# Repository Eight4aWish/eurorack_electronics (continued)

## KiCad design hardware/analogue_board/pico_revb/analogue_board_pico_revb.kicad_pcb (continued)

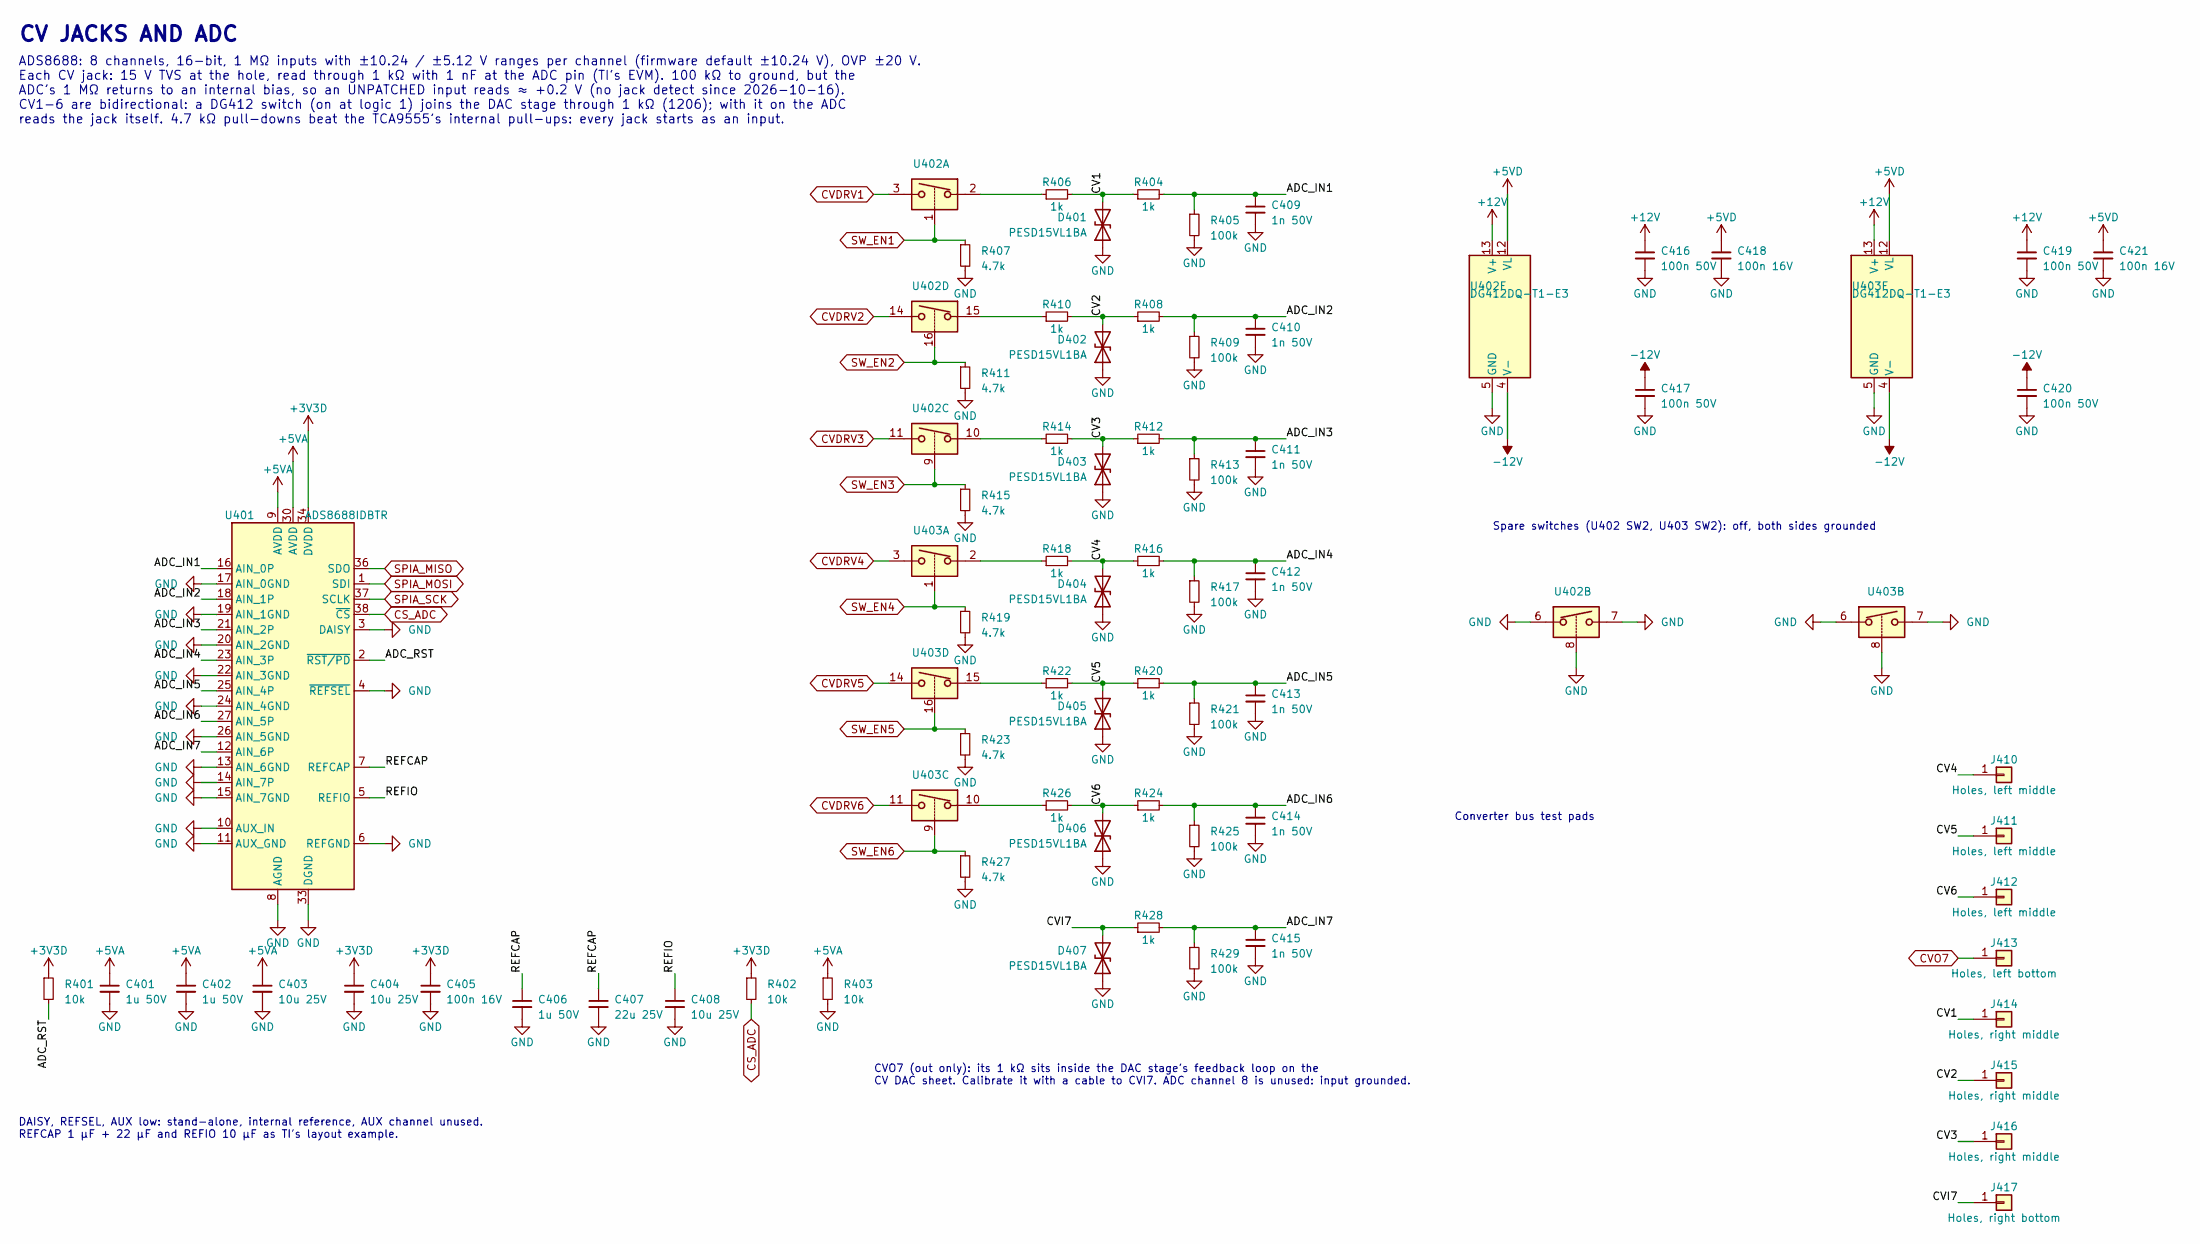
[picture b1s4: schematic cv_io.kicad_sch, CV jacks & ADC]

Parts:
C401, C402, C406: 1u 50V; C_0603_1608Metric; Voltage 50V; LCSC C15849
C403, C404, C408: 10u 25V; C_0805_2012Metric; Voltage 25V; LCSC C15850
C405, C418, C421: 100n 16V; C_0402_1005Metric; Voltage 16V; LCSC C1525
C407: 22u 25V; C_1206_3216Metric; Voltage 25V; LCSC C12891
C409, C410, C411, C412, C413, C414, C415: 1n 50V; C_0402_1005Metric; Voltage 50V; LCSC C1523
C416, C417, C419, C420: 100n 50V; C_0603_1608Metric; Voltage 50V; LCSC C14663
D401, D402, D403, D404, D405, D406, D407: PESD15VL1BA; D_SOD-323; MPN PESD15VL1BA,115; LCSC C85378
J410, J411, J412: Holes, left middle; WiringHoles_1x01; JLC bare holes
J413: Holes, left bottom; WiringHoles_1x01; JLC bare holes
J414, J415, J416: Holes, right middle; WiringHoles_1x01; JLC bare holes
J417: Holes, right bottom; WiringHoles_1x01; JLC bare holes
R401, R402, R403: 10k; R_0402_1005Metric; Tolerance 1%; LCSC C25744
R404, R408, R412, R416, R420, R424, R428: 1k; R_0402_1005Metric; Tolerance 1%; LCSC C11702
R405, R409, R413, R417, R421, R425, R429: 100k; R_0402_1005Metric; Tolerance 1%; LCSC C25741
R406, R410, R414, R418, R422, R426: 1k; R_1206_3216Metric; Tolerance 1%; LCSC C4410
R407, R411, R415, R419, R423, R427: 4.7k; R_0402_1005Metric; Tolerance 1%; LCSC C25900
U401: ADS8688IDBTR; TSSOP-38_4.4x9.7mm_P0.5mm; MPN ADS8688IDBTR; LCSC C527390
U402, U403: DG412DQ-T1-E3; TSSOP-16_4.4x5mm_P0.65mm; MPN DG412DQ-T1-E3; LCSC C2651920

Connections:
+3V3D: C404.1, C405.1, R401.1, R402.1, U401.34 (DVDD); also elsewhere on the board
+5VA: C401.1, C402.1, C403.1, R403.1, U401.9 (AVDD), U401.30 (AVDD); also elsewhere on the board
+5VD: C418.1, C421.1, U402.12 (VL), U403.12 (VL); also elsewhere on the board
+12V: C416.1, C419.1, U402.13 (V+), U403.13 (V+); also elsewhere on the board
-12V: C417.1, C420.1, U402.4 (V-), U403.4 (V-); also elsewhere on the board
/CV jacks & ADC/ADC_IN1: C409.1, R404.2, R405.1, U401.16 (AIN_0P)
/CV jacks & ADC/ADC_IN2: C410.1, R408.2, R409.1, U401.18 (AIN_1P)
/CV jacks & ADC/ADC_IN3: C411.1, R412.2, R413.1, U401.21 (AIN_2P)
/CV jacks & ADC/ADC_IN4: C412.1, R416.2, R417.1, U401.23 (AIN_3P)
/CV jacks & ADC/ADC_IN5: C413.1, R420.2, R421.1, U401.25 (AIN_4P)
/CV jacks & ADC/ADC_IN6: C414.1, R424.2, R425.1, U401.27 (AIN_5P)
/CV jacks & ADC/ADC_IN7: C415.1, R428.2, R429.1, U401.12 (AIN_6P)
/CV jacks & ADC/ADC_RST: R401.2, U401.2 (~RST/PD)
/CV jacks & ADC/CV1: D401.2 (A2), J414.1, R404.1, R406.2
/CV jacks & ADC/CV2: D402.2 (A2), J415.1, R408.1, R410.2
/CV jacks & ADC/CV3: D403.2 (A2), J416.1, R412.1, R414.2
/CV jacks & ADC/CV4: D404.2 (A2), J410.1, R416.1, R418.2
/CV jacks & ADC/CV5: D405.2 (A2), J411.1, R420.1, R422.2
/CV jacks & ADC/CV6: D406.2 (A2), J412.1, R424.1, R426.2
/CV jacks & ADC/CVI7: D407.2 (A2), J417.1, R428.1
/CV jacks & ADC/REFCAP: C406.1, C407.1, U401.7 (REFCAP)
/CV jacks & ADC/REFIO: C408.1, U401.5 (REFIO)
CS_ADC: R402.2, U401.38 (~CS); also elsewhere on the board
CVDRV1: U402.3; also elsewhere on the board
CVDRV2: U402.14; also elsewhere on the board
CVDRV3: U402.11; also elsewhere on the board
CVDRV4: U403.3; also elsewhere on the board
CVDRV5: U403.14; also elsewhere on the board
CVDRV6: U403.11; also elsewhere on the board
CVO7: J413.1; also elsewhere on the board
GND: C401.2, C402.2, C403.2, C404.2, C405.2, C406.2, C407.2, C408.2, C409.2, C410.2, C411.2, C412.2, C413.2, C414.2, C415.2, C416.2, C417.2, C418.2, C419.2, C420.2, C421.2, D401.1 (A1), D402.1 (A1), D403.1 (A1), D404.1 (A1), D405.1 (A1), D406.1 (A1), D407.1 (A1), R403.2, R405.2, R407.2, R409.2, R411.2, R413.2, R415.2, R417.2, R419.2, R421.2, R423.2, R425.2, R427.2, R429.2, U401.3 (DAISY), U401.4 (~REFSEL), U401.6 (REFGND), U401.8 (AGND), U401.10 (AUX_IN), U401.11 (AUX_GND), U401.13 (AIN_6GND), U401.14 (AIN_7P), U401.15 (AIN_7GND), U401.17 (AIN_0GND), U401.19 (AIN_1GND), U401.20 (AIN_2GND), U401.22 (AIN_3GND), U401.24 (AIN_4GND), U401.26 (AIN_5GND), U401.28 (AGND), U401.29 (AGND), U401.31 (AGND), U401.32 (AGND), U401.33 (DGND), U402.5 (GND), U402.6, U402.7, U402.8, U403.5 (GND), U403.6, U403.7, U403.8; also elsewhere on the board
unnamed: R406.1, U402.2
unnamed: R410.1, U402.15
unnamed: R414.1, U402.10
unnamed: R418.1, U403.2
unnamed: R422.1, U403.15
unnamed: R426.1, U403.10
SPIA_MISO: U401.36 (SDO); also elsewhere on the board
SPIA_MOSI: U401.1 (SDI); also elsewhere on the board
SPIA_SCK: U401.37 (SCLK); also elsewhere on the board
SW_EN1: R407.1, U402.1; also elsewhere on the board
SW_EN2: R411.1, U402.16; also elsewhere on the board
SW_EN3: R415.1, U402.9; also elsewhere on the board
SW_EN4: R419.1, U403.1; also elsewhere on the board
SW_EN5: R423.1, U403.16; also elsewhere on the board
SW_EN6: R427.1, U403.9; also elsewhere on the board

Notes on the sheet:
CV JACKS AND ADC
ADS8688: 8 channels, 16-bit, 1 MΩ inputs with ±10.24 / ±5.12 V ranges per channel (firmware default ±10.24 V), OVP ±20 V. Each CV jack: 15 V TVS at the hole, read through 1 kΩ with 1 nF at the ADC pin (TI's EVM). 100 kΩ to ground, but the ADC's 1 MΩ returns to an internal bias, so an UNPATCHED inpu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
DAISY, REFSEL, AUX low: stand-alone, internal reference, AUX channel unused. REFCAP 1 µF + 22 µF and REFIO 10 µF as TI's layout example.
CVO7 (out only): its 1 kΩ sits inside the DAC stage's feedback loop on the CV DAC sheet. Calibrate it with a cable to CVI7. ADC channel 8 is unused: input grounded.
Spare switches (U402 SW2, U403 SW2): off, both sides grounded
Converter bus test pads

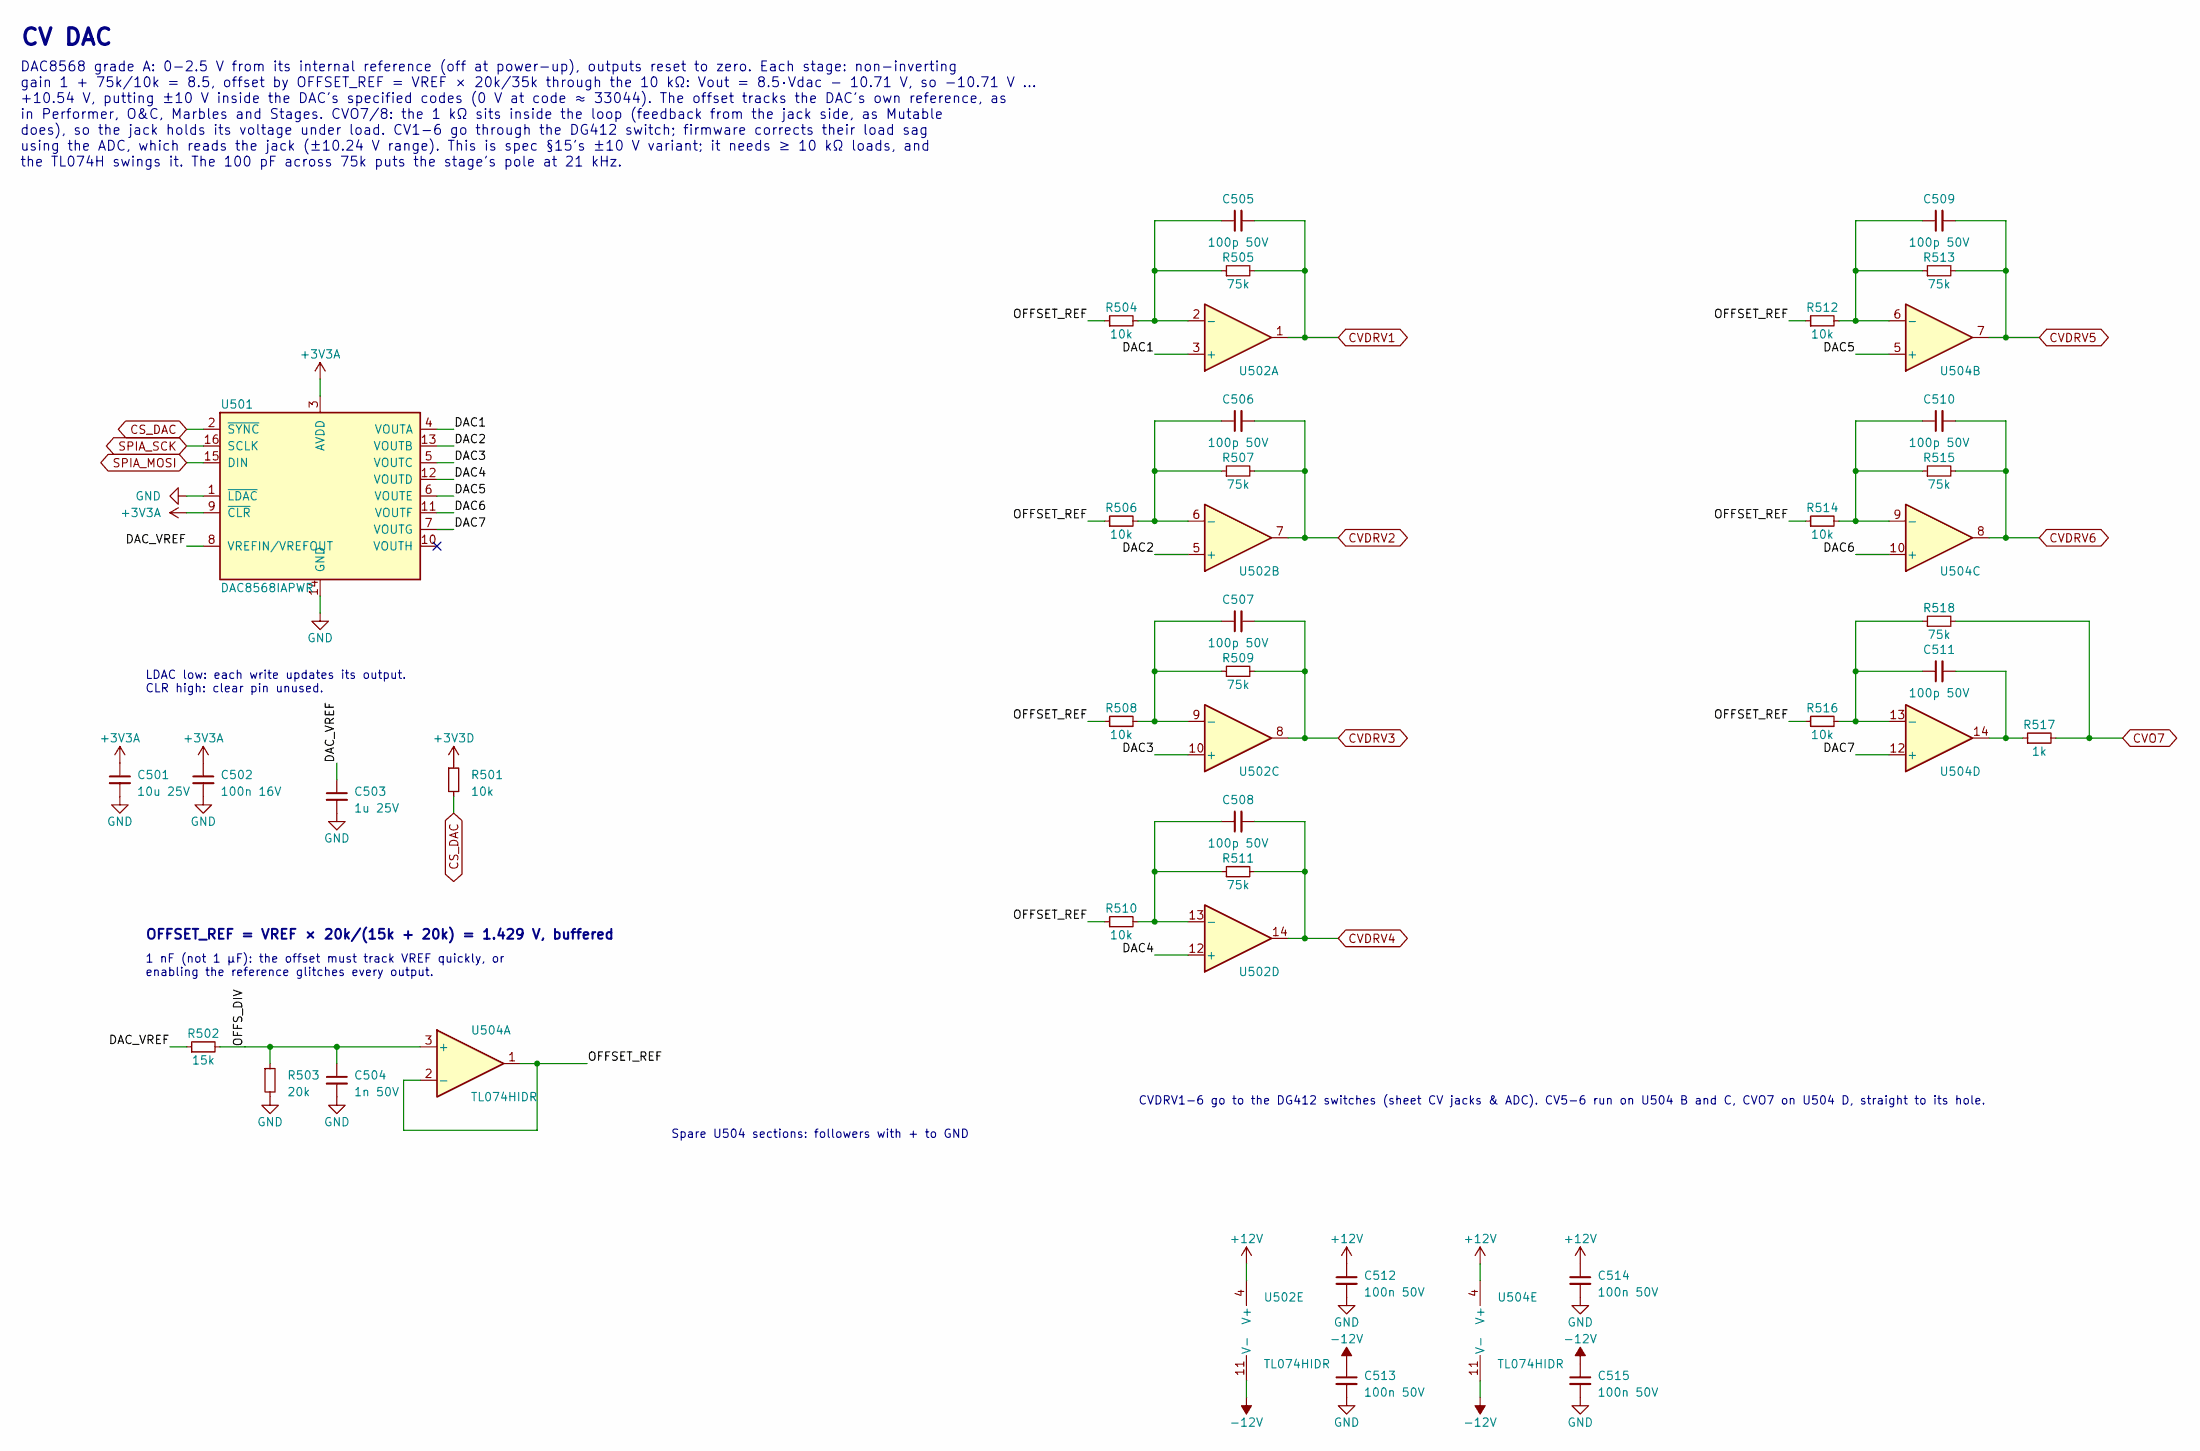
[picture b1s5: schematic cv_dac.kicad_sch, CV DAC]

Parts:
C501: 10u 25V; C_0805_2012Metric; Voltage 25V; LCSC C15850
C502: 100n 16V; C_0402_1005Metric; Voltage 16V; LCSC C1525
C503: 1u 25V; C_0402_1005Metric; Voltage 25V; LCSC C52923
C504: 1n 50V; C_0402_1005Metric; Voltage 50V; LCSC C1523
C505, C506, C507, C508, C509, C510, C511: 100p 50V; C_0402_1005Metric; Voltage 50V; LCSC C1546
C512, C513, C514, C515: 100n 50V; C_0603_1608Metric; Voltage 50V; LCSC C14663
R501, R504, R506, R508, R510, R512, R514, R516: 10k; R_0402_1005Metric; Tolerance 1%; LCSC C25744
R502: 15k; R_0402_1005Metric; Tolerance 1%; LCSC C25756
R503: 20k; R_0402_1005Metric; Tolerance 1%; LCSC C25765
R505, R507, R509, R511, R513, R515, R518: 75k; R_0603_1608Metric; Tolerance 1%; LCSC C23242
R517: 1k; R_1206_3216Metric; Tolerance 1%; LCSC C4410
U501: DAC8568IAPWR; TSSOP-16_4.4x5mm_P0.65mm; MPN DAC8568IAPWR; LCSC C486051
U502, U504: TL074HIDR; SOIC-14_3.9x8.7mm_P1.27mm; MPN TL074HIDR; LCSC C2878713

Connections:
+3V3A: C501.1, C502.1, U501.3 (AVDD), U501.9 (~CLR); also elsewhere on the board
+3V3D: R501.1; also elsewhere on the board
+12V: C512.1, C514.1, U502.4 (V+), U504.4 (V+); also elsewhere on the board
-12V: C513.1, C515.1, U502.11 (V-), U504.11 (V-); also elsewhere on the board
/CV DAC/DAC1: U501.4 (VOUTA), U502.3 (+)
/CV DAC/DAC2: U501.13 (VOUTB), U502.5 (+)
/CV DAC/DAC3: U501.5 (VOUTC), U502.10 (+)
/CV DAC/DAC4: U501.12 (VOUTD), U502.12 (+)
/CV DAC/DAC5: U501.6 (VOUTE), U504.5 (+)
/CV DAC/DAC6: U501.11 (VOUTF), U504.10 (+)
/CV DAC/DAC7: U501.7 (VOUTG), U504.12 (+)
/CV DAC/DAC_VREF: C503.1, R502.1, U501.8 (VREFIN/VREFOUT)
/CV DAC/OFFSET_REF: R504.1, R506.1, R508.1, R510.1, R512.1, R514.1, R516.1, U504.1, U504.2 (-)
/CV DAC/OFFS_DIV: C504.1, R502.2, R503.1, U504.3 (+)
CS_DAC: R501.2, U501.2 (~SYNC); also elsewhere on the board
CVDRV1: C505.2, R505.2, U502.1; also elsewhere on the board
CVDRV2: C506.2, R507.2, U502.7; also elsewhere on the board
CVDRV3: C507.2, R509.2, U502.8; also elsewhere on the board
CVDRV4: C508.2, R511.2, U502.14; also elsewhere on the board
CVDRV5: C509.2, R513.2, U504.7; also elsewhere on the board
CVDRV6: C510.2, R515.2, U504.8; also elsewhere on the board
CVO7: R517.2, R518.2; also elsewhere on the board
GND: C501.2, C502.2, C503.2, C504.2, C512.2, C513.2, C514.2, C515.2, R503.2, U501.1 (~LDAC), U501.14 (GND); also elsewhere on the board
unnamed: C511.2, R517.1, U504.14
unnamed: C505.1, R504.2, R505.1, U502.2 (-)
unnamed: C506.1, R506.2, R507.1, U502.6 (-)
unnamed: C507.1, R508.2, R509.1, U502.9 (-)
unnamed: C508.1, R510.2, R511.1, U502.13 (-)
unnamed: C509.1, R512.2, R513.1, U504.6 (-)
unnamed: C510.1, R514.2, R515.1, U504.9 (-)
unnamed: C511.1, R516.2, R518.1, U504.13 (-)
SPIA_MOSI: U501.15 (DIN); also elsewhere on the board
SPIA_SCK: U501.16 (SCLK); also elsewhere on the board

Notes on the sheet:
CV DAC
DAC8568 grade A: 0-2.5 V from its internal reference (off at power-up), outputs reset to zero. Each stage: non-inverting gain 1 + 75k/10k = 8.5, offset by OFFSET_REF = VREF × 20k/35k through the 10 kΩ: Vout = 8.5·Vdac − 10.71 V, so −10.71 V … +10.54 V, putting ±10 V inside the DAC's specified codes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
LDAC low: each write updates its output. CLR high: clear pin unused.
OFFSET_REF = VREF × 20k/(15k + 20k) = 1.429 V, buffered
1 nF (not 1 µF): the offset must track VREF quickly, or enabling the reference glitches every output.
CVDRV1-6 go to the DG412 switches (sheet CV jacks & ADC). CV5-6 run on U504 B and C, CVO7 on U504 D, straight to its hole.
Spare U504 sections: followers with + to GND

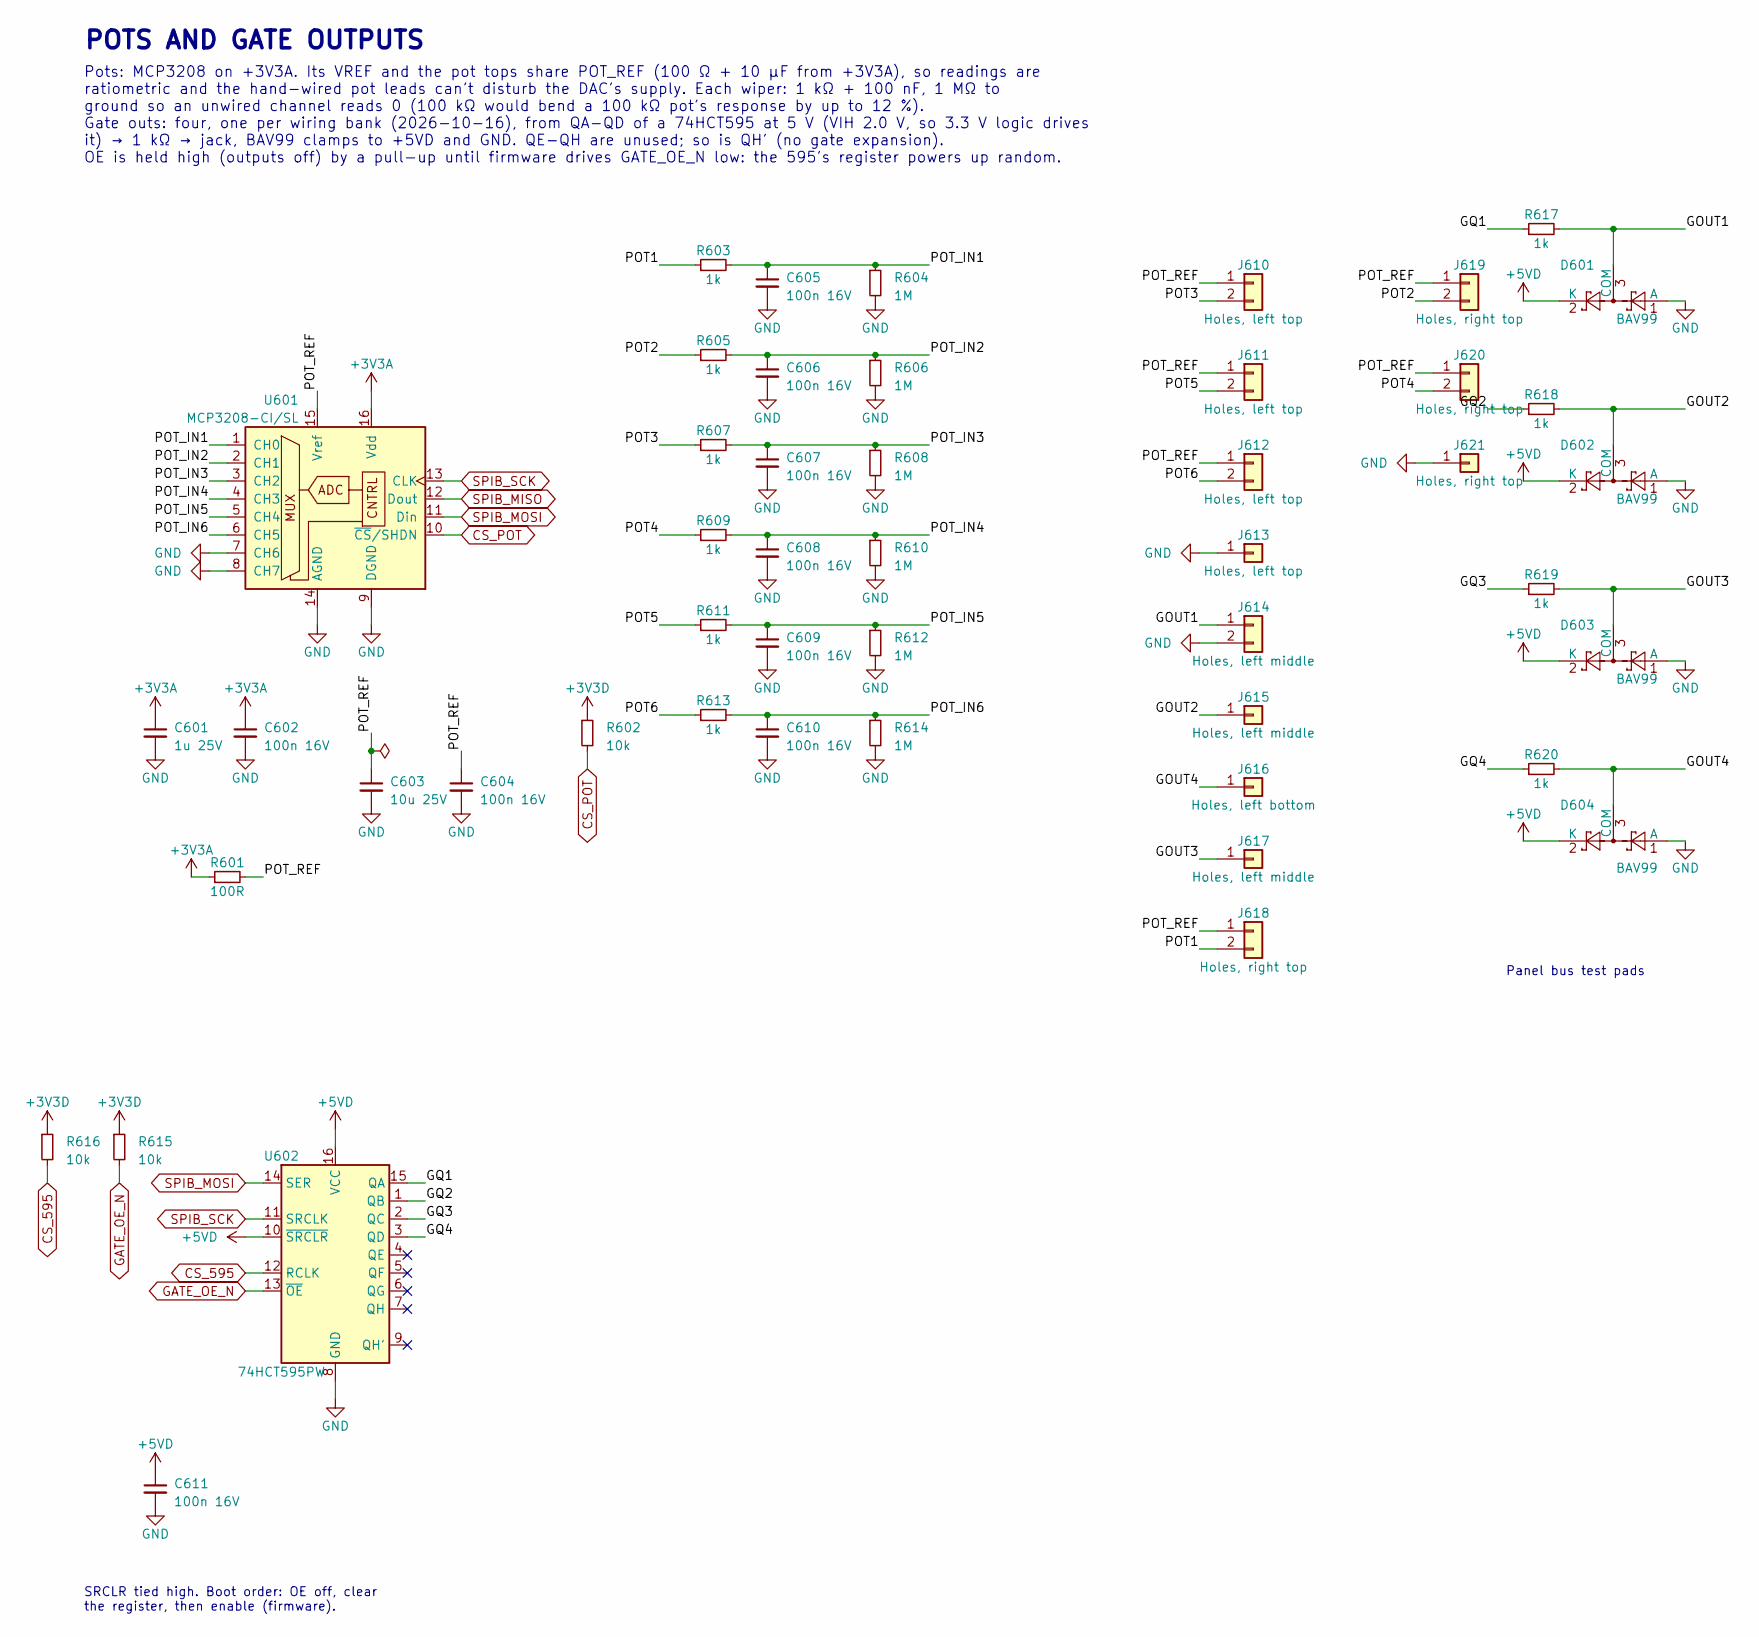
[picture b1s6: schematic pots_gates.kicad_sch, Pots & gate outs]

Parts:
C601: 1u 25V; C_0402_1005Metric; Voltage 25V; LCSC C52923
C602, C604, C605, C606, C607, C608, C609, C610, C611: 100n 16V; C_0402_1005Metric; Voltage 16V; LCSC C1525
C603: 10u 25V; C_0805_2012Metric; Voltage 25V; LCSC C15850
D601, D602, D603, D604: BAV99; SOT-23; MPN BAV99,215; LCSC C2500
J610, J611, J612: Holes, left top; WiringHoles_1x02; JLC bare holes
J613: Holes, left top; WiringHoles_1x01_G1; JLC bare holes
J614: Holes, left middle; WiringHoles_1x02_G2; JLC bare holes
J615, J617: Holes, left middle; WiringHoles_1x01; JLC bare holes
J616: Holes, left bottom; WiringHoles_1x01; JLC bare holes
J618, J619, J620: Holes, right top; WiringHoles_1x02; JLC bare holes
J621: Holes, right top; WiringHoles_1x01_G1; JLC bare holes
R601: 100R; R_0805_2012Metric; Tolerance 1%; LCSC C17408
R602, R615, R616: 10k; R_0402_1005Metric; Tolerance 1%; LCSC C25744
R603, R605, R607, R609, R611, R613, R617, R618, R619, R620: 1k; R_0402_1005Metric; Tolerance 1%; LCSC C11702
R604, R606, R608, R610, R612, R614: 1M; R_0402_1005Metric; Tolerance 1%; LCSC C26083
U601: MCP3208-CI/SL; SOIC-16_3.9x9.9mm_P1.27mm; MPN MCP3208-CI/SL; LCSC C16939
U602: 74HCT595PW; TSSOP-16_4.4x5mm_P0.65mm; MPN 74HCT595PW,118; LCSC C99710

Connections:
+3V3A: C601.1, C602.1, R601.1, U601.16 (Vdd); also elsewhere on the board
+3V3D: R602.1, R615.1, R616.1; also elsewhere on the board
+5VD: C611.1, D601.2 (K), D602.2 (K), D603.2 (K), D604.2 (K), U602.10 (~SRCLR), U602.16 (VCC); also elsewhere on the board
/Pots & gate outs/GOUT1: D601.3 (COM), J614.1, R617.2
/Pots & gate outs/GOUT2: D602.3 (COM), J615.1, R618.2
/Pots & gate outs/GOUT3: D603.3 (COM), J617.1, R619.2
/Pots & gate outs/GOUT4: D604.3 (COM), J616.1, R620.2
/Pots & gate outs/GQ1: R617.1, U602.15 (QA)
/Pots & gate outs/GQ2: R618.1, U602.1 (QB)
/Pots & gate outs/GQ3: R619.1, U602.2 (QC)
/Pots & gate outs/GQ4: R620.1, U602.3 (QD)
/Pots & gate outs/POT1: J618.2, R603.1
/Pots & gate outs/POT2: J619.2, R605.1
/Pots & gate outs/POT3: J610.2, R607.1
/Pots & gate outs/POT4: J620.2, R609.1
/Pots & gate outs/POT5: J611.2, R611.1
/Pots & gate outs/POT6: J612.2, R613.1
/Pots & gate outs/POT_IN1: C605.1, R603.2, R604.1, U601.1 (CH0)
/Pots & gate outs/POT_IN2: C606.1, R605.2, R606.1, U601.2 (CH1)
/Pots & gate outs/POT_IN3: C607.1, R607.2, R608.1, U601.3 (CH2)
/Pots & gate outs/POT_IN4: C608.1, R609.2, R610.1, U601.4 (CH3)
/Pots & gate outs/POT_IN5: C609.1, R611.2, R612.1, U601.5 (CH4)
/Pots & gate outs/POT_IN6: C610.1, R613.2, R614.1, U601.6 (CH5)
/Pots & gate outs/POT_REF: C603.1, C604.1, J610.1, J611.1, J612.1, J618.1, J619.1, J620.1, R601.2, U601.15 (Vref)
CS_595: R616.2, U602.12 (RCLK); also elsewhere on the board
CS_POT: R602.2, U601.10 (~CS/SHDN); also elsewhere on the board
GATE_OE_N: R615.2, U602.13 (~OE); also elsewhere on the board
GND: C601.2, C602.2, C603.2, C604.2, C605.2, C606.2, C607.2, C608.2, C609.2, C610.2, C611.2, D601.1 (A), D602.1 (A), D603.1 (A), D604.1 (A), J613.1, J614.2, J621.1, R604.2, R606.2, R608.2, R610.2, R612.2, R614.2, U601.7 (CH6), U601.8 (CH7), U601.9 (DGND), U601.14 (AGND), U602.8 (GND); also elsewhere on the board
SPIB_MISO: U601.12 (Dout); also elsewhere on the board
SPIB_MOSI: U601.11 (Din), U602.14 (SER); also elsewhere on the board
SPIB_SCK: U601.13 (CLK), U602.11 (SRCLK); also elsewhere on the board

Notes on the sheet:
POTS AND GATE OUTPUTS
Pots: MCP3208 on +3V3A. Its VREF and the pot tops share POT_REF (100 Ω + 10 µF from +3V3A), so readings are ratiometric and the hand-wired pot leads can't disturb the DAC's supply. Each wiper: 1 kΩ + 100 nF, 1 MΩ to ground so an unwired channel reads 0 (100 kΩ would bend a 100 kΩ pot's response by 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
SRCLR tied high. Boot order: OE off, clear the register, then enable (firmware).
Panel bus test pads

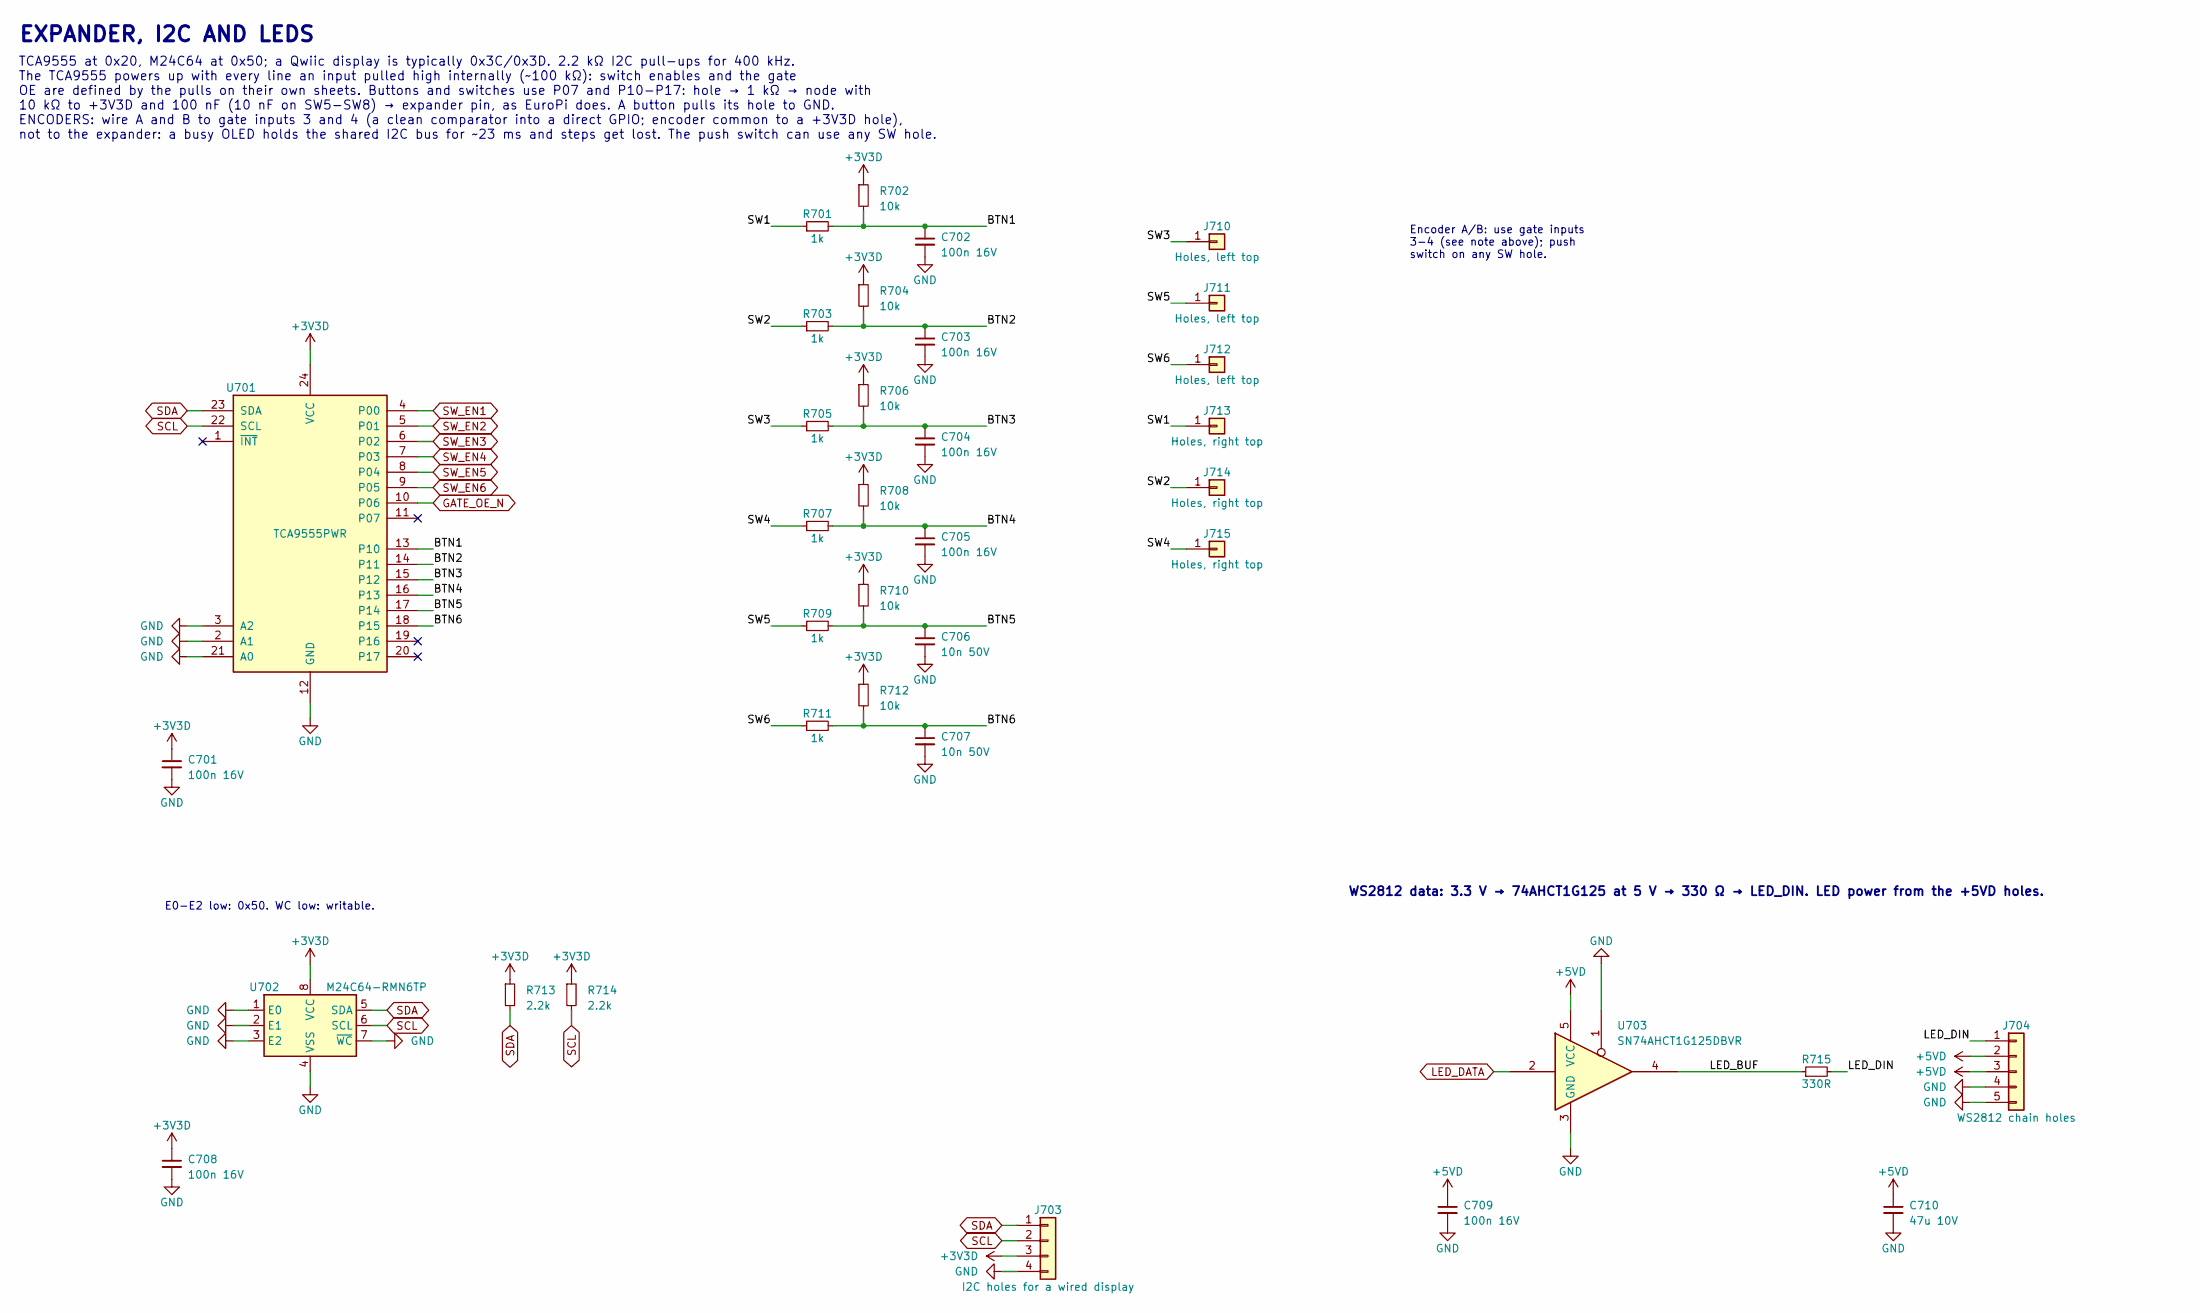
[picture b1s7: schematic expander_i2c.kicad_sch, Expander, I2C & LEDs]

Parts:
C701, C702, C703, C704, C705, C708, C709: 100n 16V; C_0402_1005Metric; Voltage 16V; LCSC C1525
C706, C707: 10n 50V; C_0402_1005Metric; Voltage 50V; LCSC C15195
C710: 47u 10V; C_1206_3216Metric; Voltage 10V; LCSC C96123
J703: I2C holes for a wired display; WiringHoles_1x04_G4; JLC bare holes
J704: WS2812 chain holes; WiringHoles_1x05_G4_5; JLC bare holes
J710, J711, J712: Holes, left top; WiringHoles_1x01; JLC bare holes
J713, J714, J715: Holes, right top; WiringHoles_1x01; JLC bare holes
R701, R703, R705, R707, R709, R711: 1k; R_0402_1005Metric; Tolerance 1%; LCSC C11702
R702, R704, R706, R708, R710, R712: 10k; R_0402_1005Metric; Tolerance 1%; LCSC C25744
R713, R714: 2.2k; R_0402_1005Metric; Tolerance 1%; LCSC C25879
R715: 330R; R_0402_1005Metric; Tolerance 1%; LCSC C25104
U701: TCA9555PWR; TSSOP-24_4.4x7.8mm_P0.65mm; MPN TCA9555PWR; LCSC C465732
U702: M24C64-RMN6TP; SOIC-8_3.9x4.9mm_P1.27mm; MPN M24C64-RMN6TP; LCSC C79988
U703: SN74AHCT1G125DBVR; SOT-23-5; MPN SN74AHCT1G125DBVR; LCSC C7484

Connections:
+3V3D: C701.1, C708.1, J703.3, R702.1, R704.1, R706.1, R708.1, R710.1, R712.1, R713.1, R714.1, U701.24 (VCC), U702.8 (VCC); also elsewhere on the board
+5VD: C709.1, C710.1, J704.2, J704.3, U703.5 (VCC); also elsewhere on the board
/Expander, I2C & LEDs/BTN1: C702.1, R701.2, R702.2, U701.13 (P10)
/Expander, I2C & LEDs/BTN2: C703.1, R703.2, R704.2, U701.14 (P11)
/Expander, I2C & LEDs/BTN3: C704.1, R705.2, R706.2, U701.15 (P12)
/Expander, I2C & LEDs/BTN4: C705.1, R707.2, R708.2, U701.16 (P13)
/Expander, I2C & LEDs/BTN5: C706.1, R709.2, R710.2, U701.17 (P14)
/Expander, I2C & LEDs/BTN6: C707.1, R711.2, R712.2, U701.18 (P15)
/Expander, I2C & LEDs/LED_BUF: R715.1, U703.4
/Expander, I2C & LEDs/LED_DIN: J704.1, R715.2
/Expander, I2C & LEDs/SW1: J713.1, R701.1
/Expander, I2C & LEDs/SW2: J714.1, R703.1
/Expander, I2C & LEDs/SW3: J710.1, R705.1
/Expander, I2C & LEDs/SW4: J715.1, R707.1
/Expander, I2C & LEDs/SW5: J711.1, R709.1
/Expander, I2C & LEDs/SW6: J712.1, R711.1
GATE_OE_N: U701.10 (P06); also elsewhere on the board
GND: C701.2, C702.2, C703.2, C704.2, C705.2, C706.2, C707.2, C708.2, C709.2, C710.2, J703.4, J704.4, J704.5, U701.2 (A1), U701.3 (A2), U701.12 (GND), U701.21 (A0), U702.1 (E0), U702.2 (E1), U702.3 (E2), U702.4 (VSS), U702.7 (~WC), U703.1, U703.3 (GND); also elsewhere on the board
LED_DATA: U703.2; also elsewhere on the board
SCL: J703.2, R714.2, U701.22 (SCL), U702.6 (SCL); also elsewhere on the board
SDA: J703.1, R713.2, U701.23 (SDA), U702.5 (SDA); also elsewhere on the board
SW_EN1: U701.4 (P00); also elsewhere on the board
SW_EN2: U701.5 (P01); also elsewhere on the board
SW_EN3: U701.6 (P02); also elsewhere on the board
SW_EN4: U701.7 (P03); also elsewhere on the board
SW_EN5: U701.8 (P04); also elsewhere on the board
SW_EN6: U701.9 (P05); also elsewhere on the board

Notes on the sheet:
EXPANDER, I2C AND LEDS
TCA9555 at 0x20, M24C64 at 0x50; a Qwiic display is typically 0x3C/0x3D. 2.2 kΩ I2C pull-ups for 400 kHz. The TCA9555 powers up with every line an input pulled high internally (~100 kΩ): switch enables and the gate OE are defined by the pulls on their own sheets. Buttons and switches use P07 and P1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
Encoder A/B: use gate inputs 3-4 (see note above); push switch on any SW hole.
E0-E2 low: 0x50. WC low: writable.
WS2812 data: 3.3 V → 74AHCT1G125 at 5 V → 330 Ω → LED_DIN. LED power from the +5VD holes.
